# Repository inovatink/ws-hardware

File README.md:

# Wearable Sensor Hardware

## Description

In this repository you can find all of the necessary materials to; 
- understand what was done 
- manufacture hardware (Electronics + 3D print)
- program Arduino bootloader
- setup microcontroller

# Important Notice

If you decide to modify any parts of the project make sure you keep it open source and share with us. Keep up the good work.

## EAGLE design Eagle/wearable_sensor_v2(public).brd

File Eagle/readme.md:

# Eagle

Eagle Schematic and Board

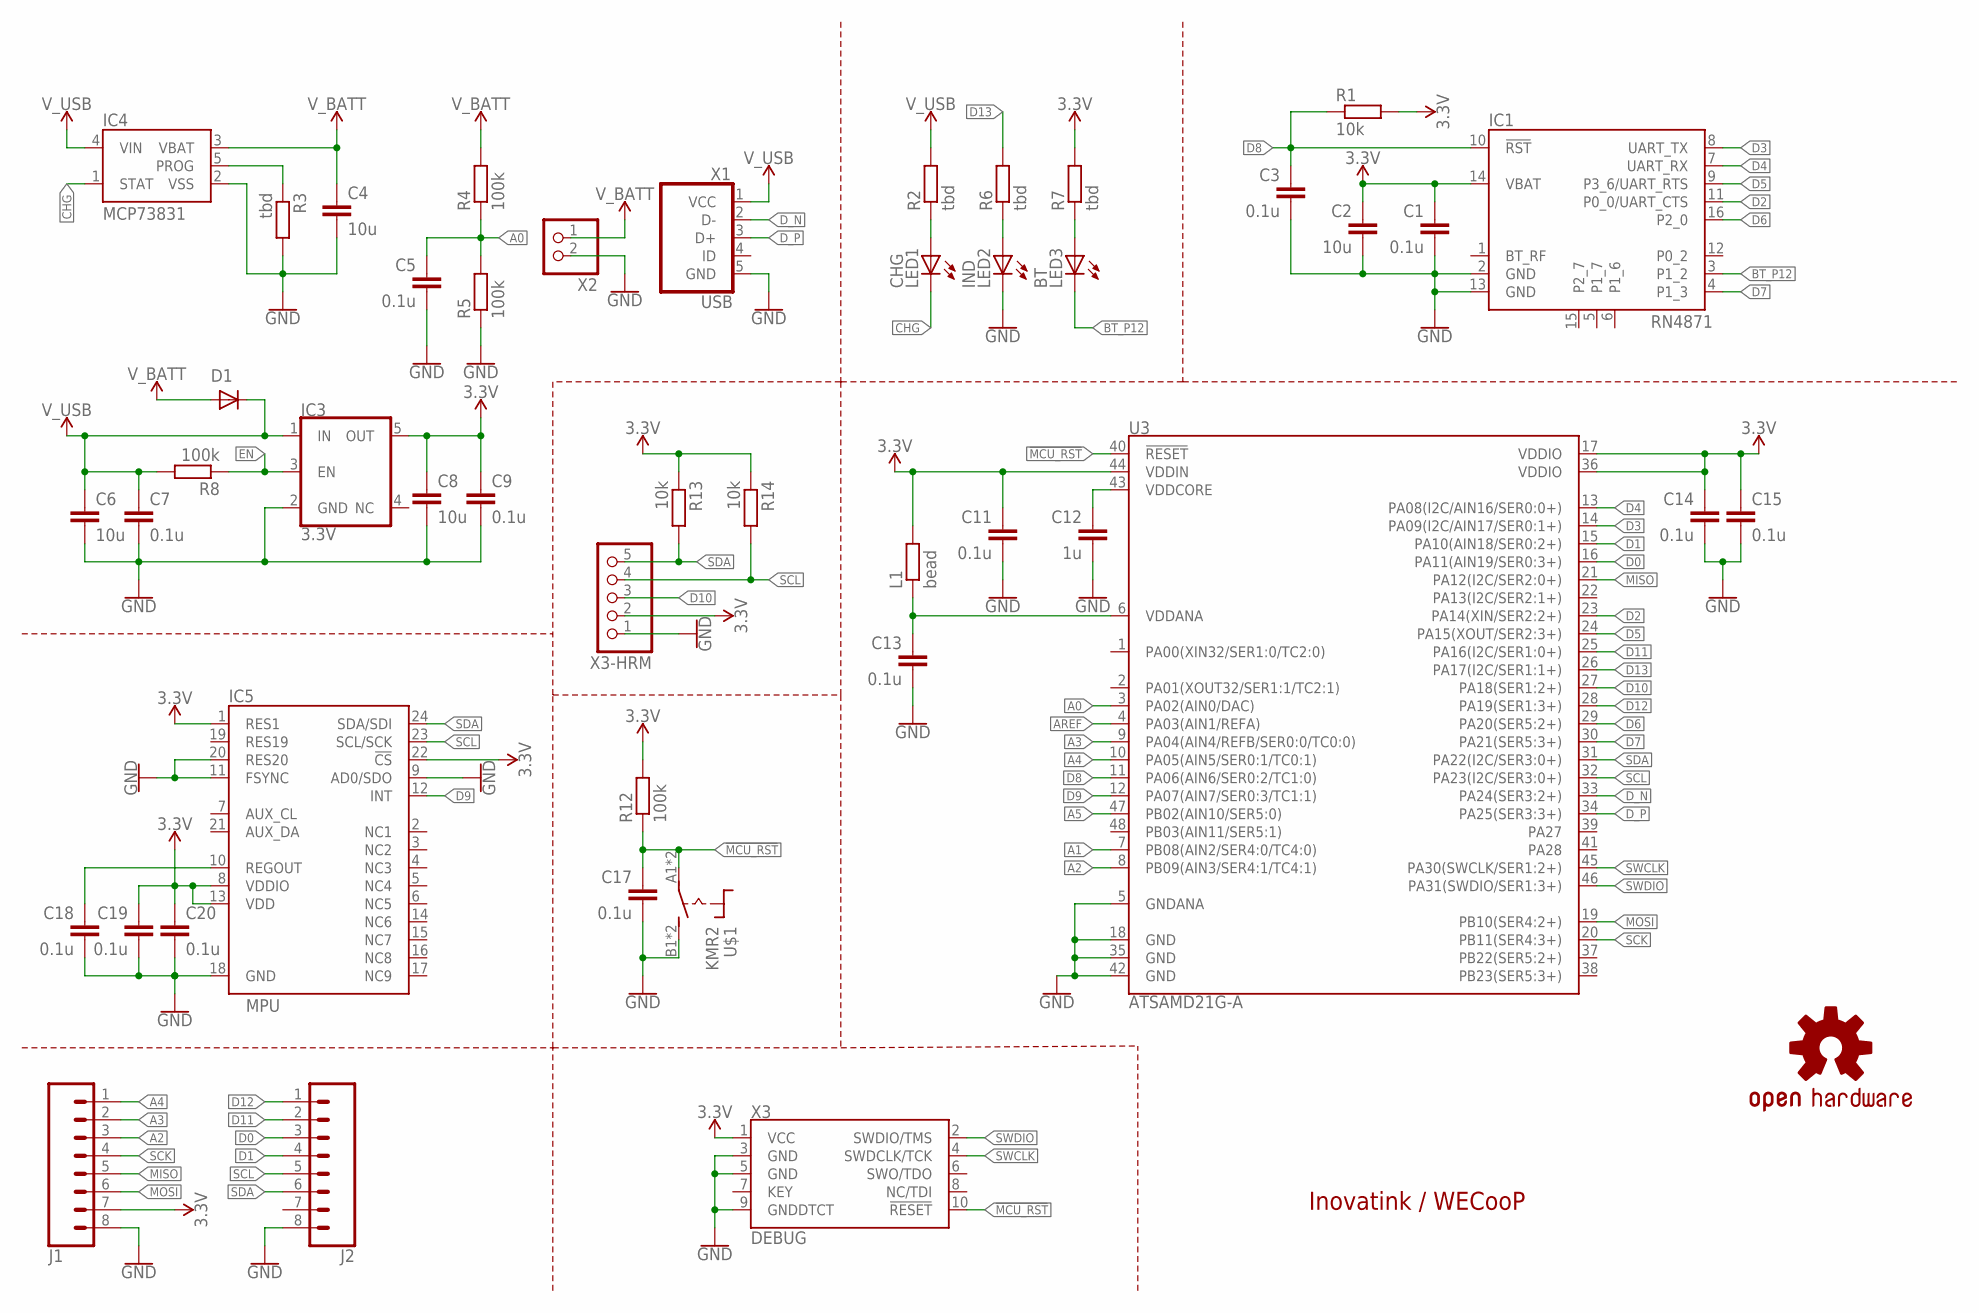
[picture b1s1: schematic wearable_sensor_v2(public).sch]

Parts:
C1, C3, C5, C7, C9, C11, C13, C14, C15, C17, C18, C19, C20: 0.1u; C0805
C2, C4, C6, C8: 10u; C0805
C12: 1u; C0805
D1: DIODESOD-323F; SOD-323F
IC1: RN4871
IC3: 3.3V; SOT23-5
IC4: MCP73831; SOT23-5
IC5: MPU; MPU9250
J1, J2: CONN_08SMD-MALE; 1X08_SMD_MALE
L1: bead; R0805
LED1: CHG; CHIP-LED0805
LED2: IND; CHIP-LED0805
LED3: BT; CHIP-LED0805
LOGO1: OSHW-LOGOMINI; OSHW-LOGO-MINI
R1, R13, R14: 10k; R0805
R2, R3, R6, R7: tbd; R0805
R4, R5, R8, R12: 100k; R0805
U3: ATSAMD21G-A; TQFP-48
U$1: KMR2
X1: USB; 10118194-0001LF
X2: JST_2PIN-SMT-RA; JST-PH-2-SMT-RA
X3: DEBUG; 2X5-PTH-1.27MM
X3-HRM: PINHD-1X5; 1X05

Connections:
3.3V: C1.1, C2.1, C8.1, C9.1, C11.1, C14.1, C15.1, C19.1, C20.1, IC1.14 (VBAT), IC3.5 (OUT), IC5.1 (RES1), IC5.8 (VDDIO), IC5.13 (VDD), IC5.22 (!CS), J1.7, L1.2, R1.2, R7.2, R12.2, R13.1, R14.1, U3.17 (VDDIO), U3.36 (VDDIO), U3.44 (VDDIN), X3.1 (VCC), X3-HRM.2
!MCU_RST: C17.1, R12.1, U3.40 (!RESET!), U$1.A1, U$1.A2, X3.10 (!RESET)
A0: C5.1, R4.1, R5.2, U3.3 (PA02(AIN0/DAC))
A1: U3.7 (PB08(AIN2/SER4:0/TC4:0))
A2: J1.3, U3.8 (PB09(AIN3/SER4:1/TC4:1))
A3: J1.2, U3.9 (PA04(AIN4/REFB/SER0:0/TC0:0))
A4: J1.1, U3.10 (PA05(AIN5/SER0:1/TC0:1))
A5: U3.47 (PB02(AIN10/SER5:0))
AREF: U3.4 (PA03(AIN1/REFA))
BT_P12: IC1.3 (P1_2), LED3.C
CHG: IC4.1 (STAT), LED1.C
D0: J2.3, U3.16 (PA11(AIN19/SER0:3+))
D1: J2.4, U3.15 (PA10(AIN18/SER0:2+))
D2: IC1.11 (P0_0/UART_CTS), U3.23 (PA14(XIN/SER2:2+))
D3: IC1.8 (UART_TX), U3.14 (PA09(I2C/AIN17/SER0:1+))
D4: IC1.7 (UART_RX), U3.13 (PA08(I2C/AIN16/SER0:0+))
D5: IC1.9 (P3_6/UART_RTS), U3.24 (PA15(XOUT/SER2:3+))
D6: IC1.16 (P2_0), U3.29 (PA20(SER5:2+))
D7: IC1.4 (P1_3), U3.30 (PA21(SER5:3+))
D8: C3.1, IC1.10 (!RST), R1.1, U3.11 (PA06(AIN6/SER0:2/TC1:0))
D9: IC5.12 (INT), U3.12 (PA07(AIN7/SER0:3/TC1:1))
D10: U3.27 (PA18(SER1:2+)), X3-HRM.3
D11: J2.2, U3.25 (PA16(I2C/SER1:0+))
D12: J2.1, U3.28 (PA19(SER1:3+))
D13: R6.2, U3.26 (PA17(I2C/SER1:1+))
D_N: U3.33 (PA24(SER3:2+)), X1.2 (D-)
D_P: U3.34 (PA25(SER3:3+)), X1.3 (D+)
EN: IC3.3 (EN), R8.1
GND: C1.2, C2.2, C3.2, C4.2, C5.2, C6.2, C7.2, C8.2, C9.2, C11.2, C12.2, C13.2, C14.2, C15.2, C17.2, C18.2, C19.2, C20.2, IC1.2 (GND), IC1.13 (GND), IC3.2 (GND), IC4.2 (VSS), IC5.9 (AD0/SDO), IC5.11 (FSYNC), IC5.18 (GND), IC5.20 (RES20), J1.8, J2.8, LED2.C, R3.2, R5.1, U3.5 (GNDANA), U3.18 (GND), U3.35 (GND), U3.42 (GND), U$1.B1 (S), U$1.B2 (S), X1.5 (GND), X2.2 (1), X3.3 (GND), X3.5 (GND), X3.9 (GNDDTCT), X3-HRM.1
MISO: J1.5, U3.21 (PA12(I2C/SER2:0+))
MOSI: J1.6, U3.19 (PB10(SER4:2+))
unnamed: LED2.A, R6.1
unnamed: LED1.A, R2.1
unnamed: IC4.5 (PROG), R3.1
unnamed: LED3.A, R7.1
unnamed: C18.1, IC5.10 (REGOUT)
unnamed: C13.1, L1.1, U3.6 (VDDANA)
unnamed: C12.1, U3.43 (VDDCORE)
SCK: J1.4, U3.20 (PB11(SER4:3+))
SCL: IC5.23 (SCL/SCK), J2.5, R14.2, U3.32 (PA23(I2C/SER3:0+)), X3-HRM.4
SDA: IC5.24 (SDA/SDI), J2.6, R13.2, U3.31 (PA22(I2C/SER3:0+)), X3-HRM.5
SWCLK: U3.45 (PA30(SWCLK/SER1:2+)), X3.4 (SWDCLK/TCK)
SWDIO: U3.46 (PA31(SWDIO/SER1:3+)), X3.2 (SWDIO/TMS)
V_BATT: C4.1, D1.A, IC4.3 (VBAT), R4.2, X2.1 (2)
V_USB: C6.1, C7.1, D1.C, IC3.1 (IN), IC4.4 (VIN), R2.2, R8.2, X1.1 (VCC)

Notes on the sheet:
Inovatink / WECooP

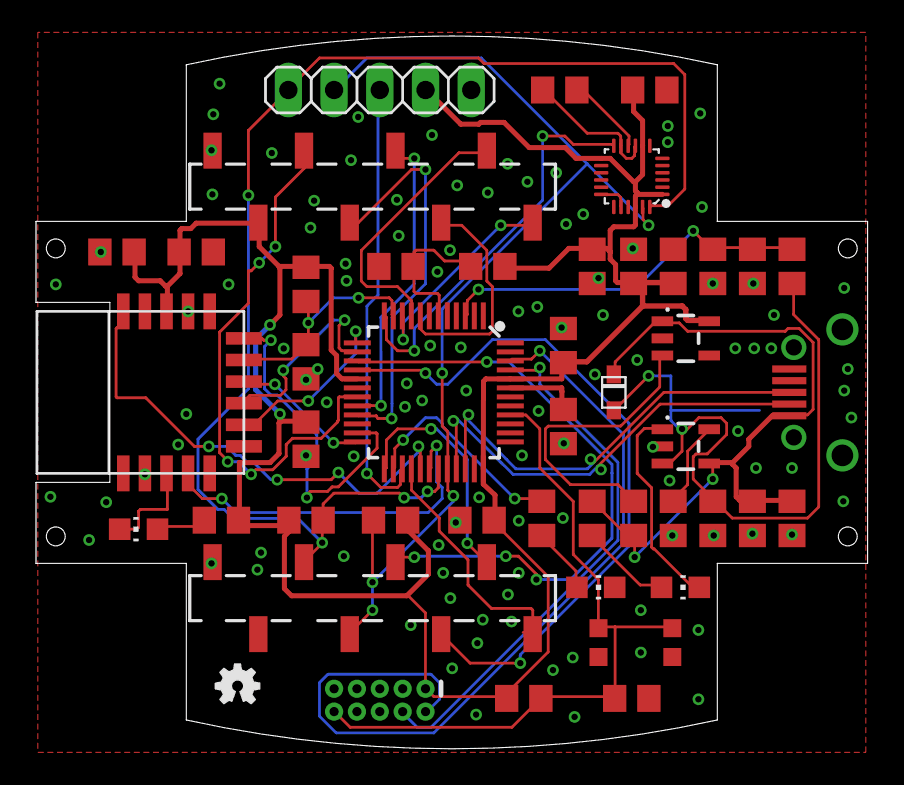
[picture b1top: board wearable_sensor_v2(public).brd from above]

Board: 2 copper layers, 46.2 x 39.6 mm, 47 parts (1 on the bottom side), 42 nets.

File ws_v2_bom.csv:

"Part";"Value";"Package";"Mfg. Part No.";"Datasheet";
;;;;
;;;;
;;;;
"B1";"button";"KMR2";"KMR231NG LFS";"https://www.ckswitches.com/media/1479/kmr2.pdf";
"C1";"0.1u";"C0805";"";"";
"C2";"10u";"C0805";"";"";
"C3";"0.1u";"C0805";"";"";
"C4";"10u";"C0805";"";"";
"C5";"0.1u";"C0805";"";"";
"C6";"10u";"C0805";" ";"";
"C7";"0.1u";"C0805";"";"";
"C8";"10u";"C0805";"";"";
"C9";"0.1u";"C0805";"";"";
"C11";"0.1u";"C0805";"";"";
"C12";"1u"; "C0805";"";"";
"C13";"0.1u";"C0805";" ";"";
"C14";"0.1u";"C0805";" ";"";
"C15";"0.1u";"C0805";" ";"";
"C17";"0.1u";"C0805";" ";"";
"C18";"0.1u";"C0805";" ";"";
"C19";"0.1u";"C0805";" ";"";
"C20";"0.1u";"C0805";" ";"";
"D1";"";"SOD-323F";"ZLLS410TA";"https://www.diodes.com/assets/Datasheets/ZLLS410.pdf";
"IC1";"RN4871";"RN4871";"RN4871-V/RM118";"http://ww1.microchip.com/downloads/en/DeviceDoc/50002489C.pdf";
"IC2";"ATSAMD21G-A";"TQFP-48";"ATSAMD21G18A-AUT";"http://ww1.microchip.com/downloads/en/DeviceDoc/40001882A.pdf";
"IC3";"AP2112K-3.3V";"SOT23-5";"AP2112K-3.3TRG1";"https://www.diodes.com/assets/Datasheets/AP2112.pdf";
"IC4";"MCP73831";"SOT23-5";"MCP73831T-2ACI/OT";"http://ww1.microchip.com/downloads/en/DeviceDoc/20001984g.pdf";
"IC5";"MPU-9250";"";"MPU-9250";"https://store.invensense.com/datasheets/invensense/MPU9250RE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";
"J1";"";"1X08_SMD_MALE";"91601-308LF";"https://cdn.amphenol-icc.com/media/wysiwyg/files/drawing/91601.pdf";
"J2";"";"1X08_SMD_MALE";"91601-308LF";"https://cdn.amphenol-icc.com/media/wysiwyg/files/drawing/91601.pdf";
"L1";"ferrite_bead";"L0805";"MH2029-601Y";"http://www.bourns.com/docs/Product-Datasheets/mh.pdf";
"LED1";"AMBER";"CHIP-LED0805";"";"";
"LED2";"GREEN";"CHIP-LED0805";"";"";
"LED3";"BLUE";"CHIP-LED0805";"";"";
"R1";"10k";"R0805";"";"";
"R2";"tbd";"R0805";"";"";
"R3";"tbd";"R0805";"";"";
"R4";"100k";"R0805";"";"";
"R5";"100k";"R0805";"";"";
"R6";"tbd";"R0805";"";"";
"R7";"tbd";"R0805";"";"";
"R8";"100k";"R0805";"";"";
"R12";"100k";"R0805";"";"";
"R13";"10k";"R0805";"";"";
"R14";"10k";"R0805";"";"";
"X1";"USB";"USB - micro B";"10118194-0001LF";"https://cdn.amphenol-icc.com/media/wysiwyg/files/documentati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";
"X2";"BATTERY";"JST_2PIN-SMT-RA";"S2B-PH-SM4-TB(LF)(SN)";"http://www.jst-mfg.com/product/pdf/eng/ePH.pdf";
"X3";"DEBUG";"2X5-PTH-1.27MM";"20021111-00010T4LF";"https://cdn.amphenol-icc.com/media/wysiwyg/files/drawing/200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";
"X4";"HRM";"1X5-PTH-2.54MM";"";"";

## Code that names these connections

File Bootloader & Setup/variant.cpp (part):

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 * +------------+------------------+--------+-----------------+--------------------------------------------------------------------------------------------------------
 * |            | Digital Low      |        |                 |
 * +------------+------------------+--------+-----------------+--------------------------------------------------------------------------------------------------------
 * | 0          | 0 -> RX          |  PA11  |                 | EIC/EXTINT[11] ADC/AIN[19]           PTC/X[3] *SERCOM0/PAD[3]  SERCOM2/PAD[3]  TCC0/WO[3]  TCC1/WO[1]
 * | 1          | 1 <- TX          |  PA10  |                 | EIC/EXTINT[10] ADC/AIN[18]           PTC/X[2] *SERCOM0/PAD[2]                  TCC0/WO[2]  TCC1/WO[0]
 * | 2          | 2                |  PA14  |                 | EIC/EXTINT[14]                                 SERCOM2/PAD[2]  SERCOM4/PAD[2]  TC3/WO[0]   TCC0/WO[4]
 * | 3          | ~3               |  PA09  |                 | EIC/EXTINT[9]  ADC/AIN[17]           PTC/X[1]  SERCOM0/PAD[1]  SERCOM2/PAD[1] *TCC0/WO[1]  TCC1/WO[3]
 * | 4          | ~4               |  PA08  |                 | EIC/NMI        ADC/AIN[16]           PTC/X[0]  SERCOM0/PAD[0]  SERCOM2/PAD[0] *TCC0/WO[0]  TCC1/WO[2]
 * | 5          | ~5               |  PA15  |                 | EIC/EXTINT[15]                                 SERCOM2/PAD[3]  SERCOM4/PAD[3] *TC3/WO[1]   TCC0/WO[5]
 * | 6          | ~6               |  PA20  |                 | EIC/EXTINT[4]                        PTC/X[8]  SERCOM5/PAD[2]  SERCOM3/PAD[2]             *TCC0/WO[6]
 * | 7          | 7                |  PA21  |                 | EIC/EXTINT[5]                        PTC/X[9]  SERCOM5/PAD[3]  SERCOM3/PAD[3]              TCC0/WO[7]
 * +------------+------------------+--------+-----------------+--------------------------------------------------------------------------------------------------------
 * |            | Digital High     |        |                 |
 * +------------+------------------+--------+-----------------+--------------------------------------------------------------------------------------------------------
 * | 8          | ~8               |  PA06  |                 | EIC/EXTINT[6]  ADC/AIN[6]  AC/AIN[2] PTC/Y[4]  SERCOM0/PAD[2]                 *TCC1/WO[0]
 * | 9          | ~9               |  PA07  |                 | EIC/EXTINT[7]  ADC/AIN[7]  AC/AIN[3] PTC/Y[5]  SERCOM0/PAD[3]                 *TCC1/WO[1]
 * | 10         | ~10              |  PA18  |                 | EIC/EXTINT[2]                        PTC/X[6] +SERCOM1/PAD[2]  SERCOM3/PAD[2] *TC3/WO[0]    TCC0/WO[2]
 * | 11         | ~11              |  PA16  |                 | EIC/EXTINT[0]                        PTC/X[4] +SERCOM1/PAD[0]  SERCOM3/PAD[0] *TCC2/WO[0]   TCC0/WO[6]
 * | 12         | ~12              |  PA19  |                 | EIC/EXTINT[3]                        PTC/X[7] +SERCOM1/PAD[3]  SERCOM3/PAD[3]  TC3/WO[1]   *TCC0/WO[3]
 * | 13         | ~13              |  PA17  | LED             | EIC/EXTINT[1]                        PTC/X[5] +SERCOM1/PAD[1]  SERCOM3/PAD[1] *TCC2/WO[1]   TCC0/WO[7]
 * +------------+------------------+--------+-----------------+--------------------------------------------------------------------------------------------------------
 * |            | Analog Connector |        |                 |
 * +------------+------------------+--------+-----------------+--------------------------------------------------------------------------------------------------------
 * | 14         | A0               |  PA02  | A0              | EIC/EXTINT[2] *ADC/AIN[0]  DAC/VOUT  PTC/Y[0]
 * | 15         | A1               |  PB08  | A1              | EIC/EXTINT[8] *ADC/AIN[2]            PTC/Y[14] SERCOM4/PAD[0]                  TC4/WO[0]
 * | 16         | A2               |  PB09  | A2              | EIC/EXTINT[9] *ADC/AIN[3]            PTC/Y[15] SERCOM4/PAD[1]                  TC4/WO[1]
 * | 17         | A3               |  PA04  | A3              | EIC/EXTINT[4] *ADC/AIN[4]  AC/AIN[0] PTC/Y[2]  SERCOM0/PAD[0]                  TCC0/WO[0]
 * | 18         | A4               |  PA05  | A4              | EIC/EXTINT[5] *ADC/AIN[5]  AC/AIN[1] PTC/Y[5]  SERCOM0/PAD[1]                  TCC0/WO[1]
 * | 19         | A5               |  PB02  | A5              | EIC/EXTINT[2] *ADC/AIN[10]           PTC/Y[8]  SERCOM5/PAD[0]
 * +------------+------------------+--------+-----------------+--------------------------------------------------------------------------------------------------------
 * |            | Wire             |        |                 |
 * +------------+------------------+--------+-----------------+--------------------------------------------------------------------------------------------------------
 * | 20         | SDA              |  PA22  | SDA             | EIC/EXTINT[6]                        PTC/X[10] *SERCOM3/PAD[0] SERCOM5/PAD[0] TC4/WO[0] TCC0/WO[4]
 * | 21         | SCL              |  PA23  | SCL             | EIC/EXTINT[7]                        PTC/X[11] *SERCOM3/PAD[1] SERCOM5/PAD[1] TC4/WO[1] TCC0/WO[5]
 * +------------+------------------+--------+-----------------+--------------------------------------------------------------------------------------------------------
 * |            |SPI (Legacy ICSP) |        |                 |
 * +------------+------------------+--------+-----------------+--------------------------------------------------------------------------------------------------------
 * | 22         | 1                |  PA12  | MISO            | EIC/EXTINT[12] SERCOM2/PAD[0] *SERCOM4/PAD[0] TCC2/WO[0] TCC0/WO[6]
 * |            | 2                |        | 5V0             |
 * | 23         | 4                |  PB10  | MOSI            | EIC/EXTINT[10]                *SERCOM4/PAD[2] TC5/WO[0]  TCC0/WO[4]
 * | 24         | 3                |  PB11  | SCK             | EIC/EXTINT[11]                *SERCOM4/PAD[3] TC5/WO[1]  TCC0/WO[5]
 * |            | 5                |        | RESET           |
 * |            | 6                |        | GND             |
 * +------------+------------------+--------+-----------------+--------------------------------------------------------------------------------------------------------
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 * |            | USB              |        |                 |
 * +------------+------------------+--------+-----------------+--------------------------------------------------------------------------------------------------------
 * | 27         |                  |  PA28  | USB_HOST_ENABLE | EIC/EXTINT[8]
 * | 28         |                  |  PA24  | USB_NEGATIVE    | *USB/DM
 * | 29         |                  |  PA25  | USB_POSITIVE    | *USB/DP
 * +------------+------------------+--------+-----------------+--------------------------------------------------------------------------------------------------------
 * |            | EDBG             |        |                 |
 * +------------+------------------+--------+-----------------+--------------------------------------------------------------------------------------------------------
 * | 30         |                  |  PB22  | EDBG_UART TX    | *SERCOM5/PAD[2]
 * | 31         |                  |  PB23  | EDBG_UART RX    | *SERCOM5/PAD[3]
 * +------------+------------------+--------+-----------------+--------------------------------------------------------------------------------------------------------
 * | 32         |                  |  PA22  | EDBG_SDA        | Pin 20 (SDA)
 * | 33         |                  |  PA23  | EDBG_SCL        | Pin 21 (SCL)
 * +------------+------------------+--------+-----------------+--------------------------------------------------------------------------------------------------------
 * | 34         |                  |  PA19  | EDBG_MISO       | EIC/EXTINT[3] *SERCOM1/PAD[3] SERCOM3/PAD[3] TC3/WO[1]  TCC0/WO[3]
 * | 35         |                  |  PA16  | EDBG_MOSI       | EIC/EXTINT[0] *SERCOM1/PAD[0] SERCOM3/PAD[0] TCC2/WO[0] TCC0/WO[6]
 * | 36         |                  |  PA18  | EDBG_SS         | EIC/EXTINT[2] *SERCOM1/PAD[2] SERCOM3/PAD[2] TC3/WO[0]  TCC0/WO[2]
 * | 37         |                  |  PA17  | EDBG_SCK        | EIC/EXTINT[1] *SERCOM1/PAD[1] SERCOM3/PAD[1] TCC2/WO[1] TCC0/WO[7]
 * +------------+------------------+--------+-----------------+--------------------------------------------------------------------------------------------------------
 * | 38         | ATN              |  PA13  | EDBG_GPIO0      | EIC/EXTINT[13] SERCOM2/PAD[1] SERCOM4/PAD[1] *TCC2/WO[1] TCC0/WO[7]
 * | 39         |                  |  PA21  | EDBG_GPIO1      | Pin 7
 * | 40         |                  |  PA06  | EDBG_GPIO2      | Pin 8
 * | 41         |                  |  PA07  | EDBG_GPIO3      | Pin 9
 * +------------+------------------+--------+-----------------+--------------------------------------------------------------------------------------------------------
 * |            |                  |        |                 |
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
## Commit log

2018-01-31 setup files
    setup files

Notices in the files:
Bootloader & Setup/variant.cpp:
Copyright (c) 2014-2015 Arduino LLC.  All right reserved.
parts and their libraries:
SparkFun-IC-Power: Licensing: Creative Commons ShareAlike 4.0 International - https://creativecommons.org/licenses/by-sa/4.0
